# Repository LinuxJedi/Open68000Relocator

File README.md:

# Open68000Relocator
Open68000Relocator is an Open Hardware adapter PCB that changes the orientation of a 68000 DIP CPU.

**Note**: This project requires KiCad 5.99 or higher.

## Summary
This is based on [SukkoPera's](https://github.com/SukkoPera/Open68000Relocator) awesome 68000 relocator. I modified it to make it easier to fit on some motherboards and better support for PiStorm. It has the following changes:

* Hole for the capacitor C816 in rev 6 and 8 Amiga 500s (and Plus).
* Re-routed 4-layer with length adjusted traces for stability with PiStorm on some Amigas.
* Better power traces, useful for PiStorm.
* Some style changes.
* A couple of decoupling capacitors (2x 100nF 0603).

## License
Open68000Relocator is Open Hardware released under the GNU General Public License (GPL) v3. If you make any modifications to the board, **you must** contribute them back.

Open68000Relocator is provided to you ‘as is’ and without any express or implied warranties whatsoever with respect to its functionality, operability or use, including, without limitation, any implied warranties of merchantability, fitness for a particular purpose or infringement. We expressly disclaim any liability whatsoever for any direct, indirect, consequential, incidental or special damages, including, without limitation, lost revenues, lost profits, losses resulting from business interruption or loss of data, regardless of the form of action or legal theory under which the liability may be asserted, even if advised of the possibility or likelihood of such damages.

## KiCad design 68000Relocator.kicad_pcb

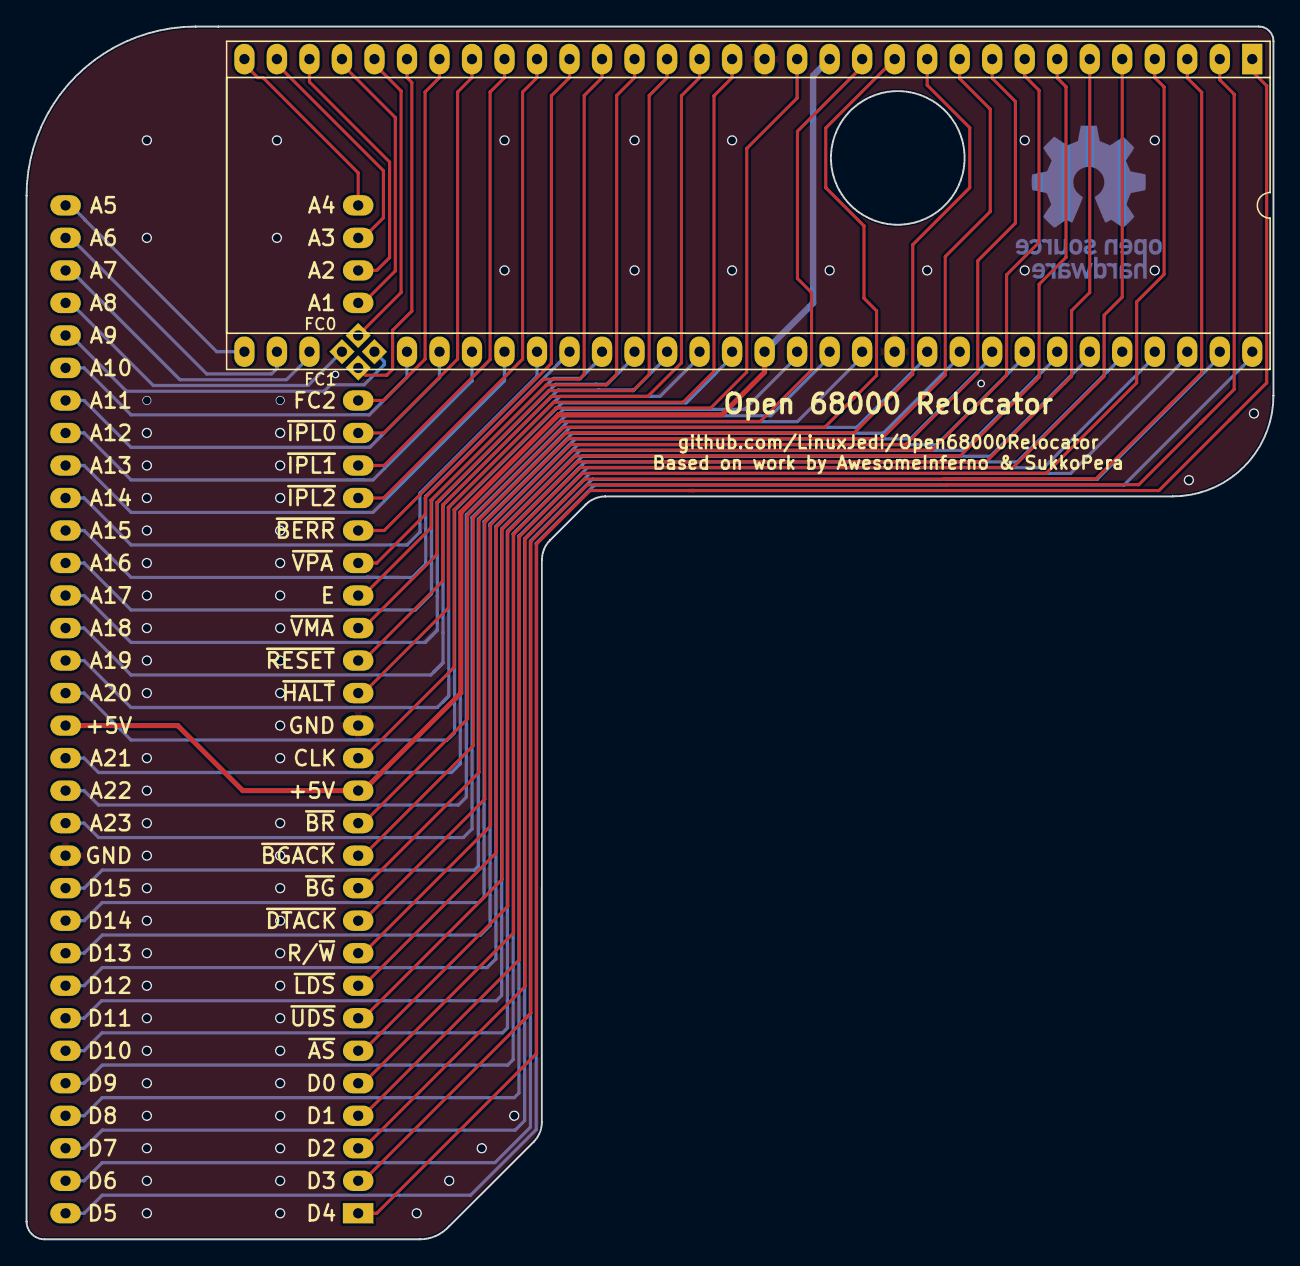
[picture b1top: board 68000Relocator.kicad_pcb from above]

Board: 2 copper layers, 97.4 x 94.7 mm, 3 parts (1 on the bottom side), 62 nets.

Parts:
P99: OSHW_LOGO; OSHW-Logo_11.4x12mm_Copper
U1: 68000D; DIP-64_W22.86mm_Socket_LongPads_Socket
U2: 68000D; DIP-64_W22.86mm_Socket_LongPads_IC

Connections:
/A1: U1.29, U2.29
/A2: U1.30, U2.30
/A3: U1.31, U2.31
/A4: U1.32, U2.32
/A5: U1.33, U2.33
/A6: U1.34, U2.34
/A7: U1.35, U2.35
/A8: U1.36, U2.36
/A9: U1.37, U2.37
/A10: U1.38, U2.38
/A11: U1.39, U2.39
/A12: U1.40, U2.40
/A13: U1.41, U2.41
/A14: U1.42, U2.42
/A15: U1.43, U2.43
/A16: U1.44, U2.44
/A17: U1.45, U2.45
/A18: U1.46, U2.46
/A19: U1.47, U2.47
/A20: U1.48, U2.48
/A21: U1.50, U2.50
/A22: U1.51, U2.51
/A23: U1.52, U2.52
/AS: U1.6, U2.6
/BERR: U1.22, U2.22
/BG: U1.11, U2.11
/BGACK: U1.12, U2.12
/BR: U1.13, U2.13
/CLK: U1.15, U2.15
/D0: U1.5, U2.5
/D1: U1.4, U2.4
/D2: U1.3, U2.3
/D3: U1.2, U2.2
/D4: U1.1, U2.1
/D5: U1.64, U2.64
/D6: U1.63, U2.63
/D7: U1.62, U2.62
/D8: U1.61, U2.61
/D9: U1.60, U2.60
/D10: U1.59, U2.59
/D11: U1.58, U2.58
/D12: U1.57, U2.57
/D13: U1.56, U2.56
/D14: U1.55, U2.55
/D15: U1.54, U2.54
/DTACK: U1.10, U2.10
/E: U1.20, U2.20
/FC0: U1.28, U2.28
/FC1: U1.27, U2.27
/FC2: U1.26, U2.26
/HALT: U1.17, U2.17
/IPL0: U1.25, U2.25
/IPL1: U1.24, U2.24
/IPL2: U1.23, U2.23
/LDS: U1.8, U2.8
/R/W: U1.9, U2.9
/RESET: U1.18, U2.18
/UDS: U1.7, U2.7
/VMA: U1.19, U2.19
/VPA: U1.21, U2.21
GND: U1.16, U1.53, U2.16, U2.53
VCC: U1.14, U1.49, U2.14, U2.49

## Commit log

2021-04-22 My spin on SukkoPera's design
    Added a hole for the capacitor in rev 6 and 8, plus a few other minor
    tweaks.
2021-07-05 New revision ready
2021-07-12 Remove old silk ver
